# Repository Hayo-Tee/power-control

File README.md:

# Power Control PC by ESP32

[🇷🇺 RU](README_ru.md) | [🇬🇧 EN](README.md)

## Project Description

Recently, I purchased a **Cooler Master Stacker 830** case and built a server PC based on the **ASUS Z10PE-D8** motherboard. Since I access the server via **Tailscale**, I faced a challenge — how to power on the PC remotely if it is completely turned off at home. There are many solutions available online, but I decided to create my own using **ESPHome** and **ESP32-C3**.

---

## Key Features

* **Power on the PC**
* **Power off the PC**
* **Force shutdown** (emulation of holding the power button)
* **Restart the PC**
* **Get PC status** (on / off)

---

## Additional Functionality for Unraid

Since my server runs **Unraid OS**, I added an extra button to control a virtual machine. You can easily repurpose this feature for any other task by modifying the script.

* **Single press** — starts the virtual machine
* **Double press** — stops the virtual machine
* **Long press** — force stops the virtual machine

---

## License

This project is distributed under the **MIT** license.

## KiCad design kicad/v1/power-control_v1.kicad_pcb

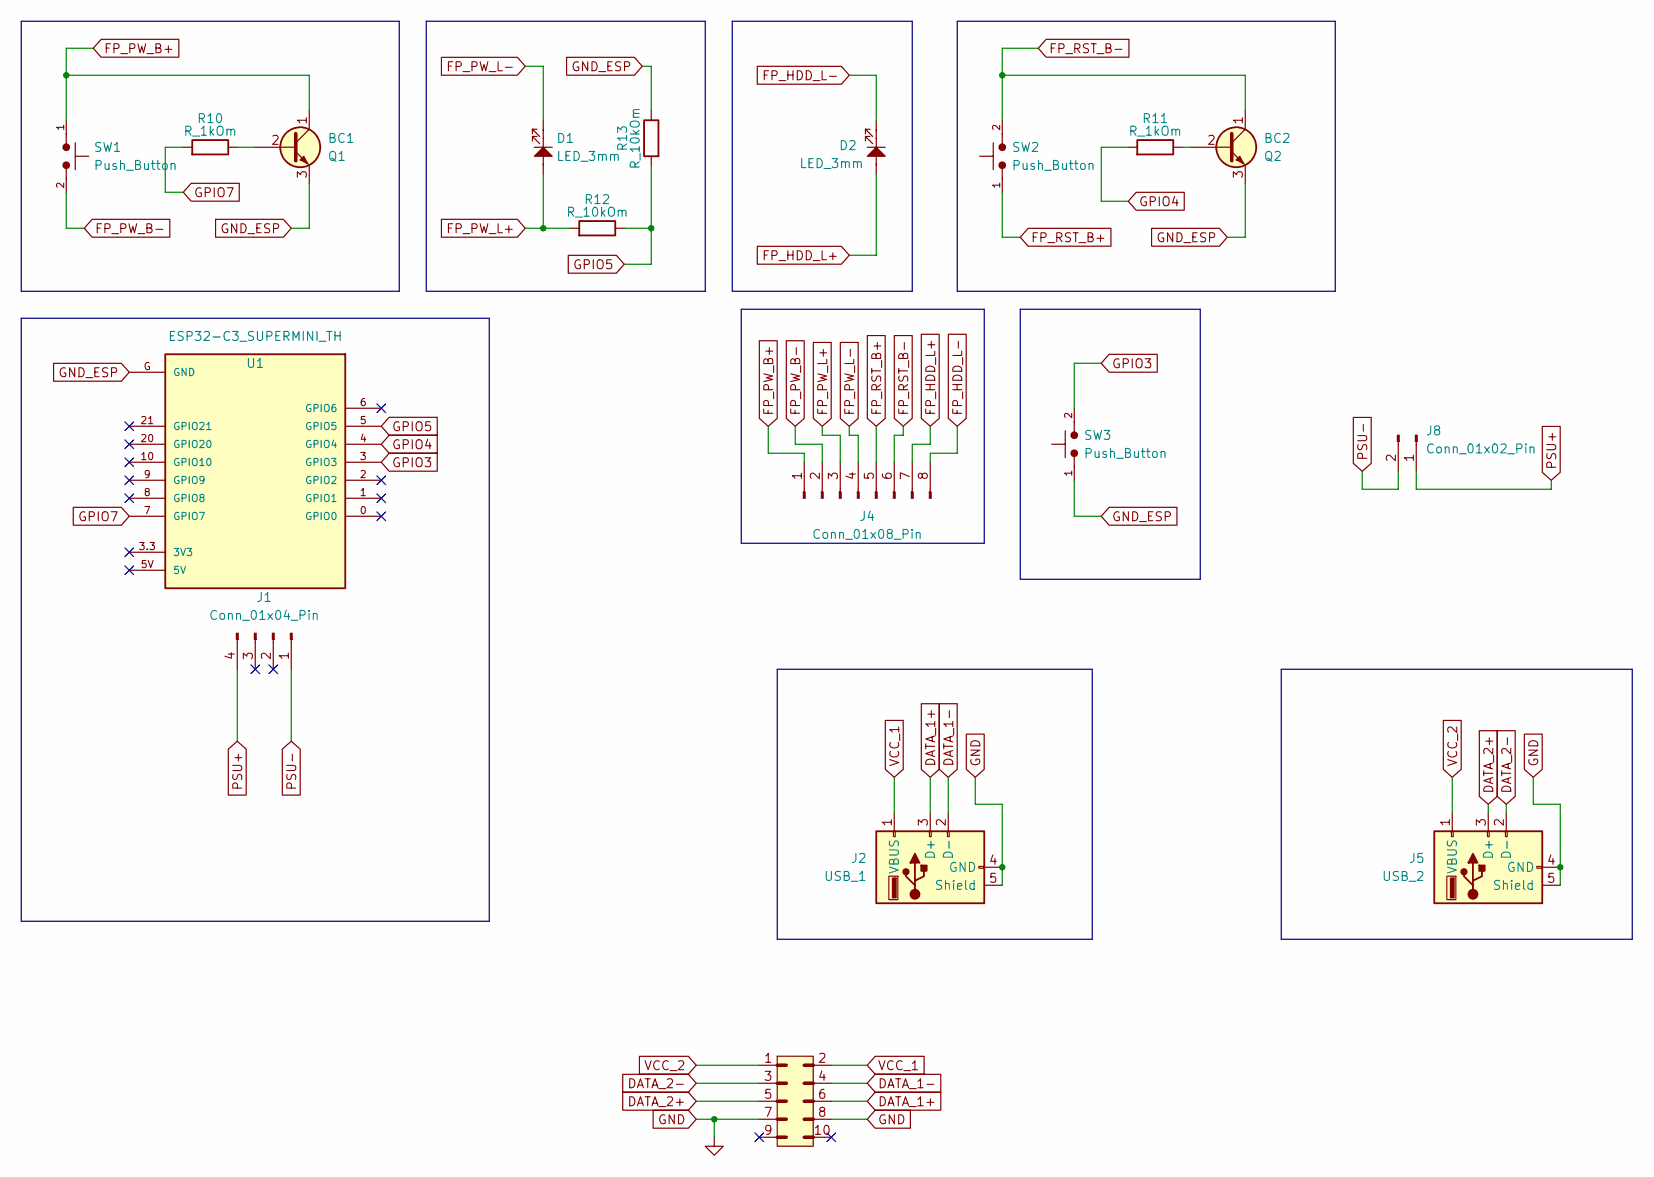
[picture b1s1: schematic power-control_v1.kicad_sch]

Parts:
BC1: Q1; TO-92_Inline_Wide_CBE
BC2: Q2; TO-92_Inline_Wide_CBE
D1, D2: LED_3mm; LED_D3.0mm
J1: Conn_01x04_Pin; PinHeader_1x04_P2.54mm_Vertical
J2: USB_1; ONSHORE_USB-A1VSB6
J4: Conn_01x08_Pin; Connector_MB_FP
J5: USB_2; ONSHORE_USB-A1VSB6
J7: PINHD_2x5_Male; PinHeader_2x05_P2.54mm_Horizontal
J8: Conn_01x02_Pin; JST_XH_B2B-XH-AM_1x02_P2.50mm_Vertical
R10, R11: R_1kOm; R_1206_3216Metric
R12, R13: R_10kOm; R_1206_3216Metric
SW1, SW2, SW3: Push_Button; SW_PUSH_6mm
U1: ESP32-C3_SUPERMINI_TH; MODULE_ESP32-C3_SUPERMINI

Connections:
DATA_1+: J2.3 (D+), J7.6
DATA_1-: J2.2 (D-), J7.4
DATA_2+: J5.3 (D+), J7.5
DATA_2-: J5.2 (D-), J7.3
FP_HDD_L+: D2.2, J4.7
FP_HDD_L-: D2.1, J4.8
FP_PW_B+: BC1.1 (C), J4.1, SW1.1
FP_PW_B-: J4.2, SW1.2
FP_PW_L+: D1.2, J4.3, R12.1
FP_PW_L-: D1.1, J4.4
FP_RST_B+: J4.5, SW2.1
FP_RST_B-: BC2.1 (C), J4.6, SW2.2
GND: J2.4 (GND), J2.5 (Shield), J2.S1, J2.S2, J5.4 (GND), J5.5 (Shield), J5.S1, J5.S2, J7.7, J7.8
GND_ESP: BC1.3 (E), BC2.3 (E), R13.2, SW3.1, U1.G (GND)
GPIO3: SW3.2, U1.3 (GPIO3)
GPIO4: R11.1, U1.4 (GPIO4)
GPIO5: R12.2, R13.1, U1.5 (GPIO5)
GPIO7: R10.1, U1.7 (GPIO7)
unnamed: BC1.2 (B), R10.2
unnamed: BC2.2 (B), R11.2
PSU+: J1.4, J8.1
PSU-: J1.1, J8.2
VCC_1: J2.1 (VBUS), J7.2
VCC_2: J5.1 (VBUS), J7.1

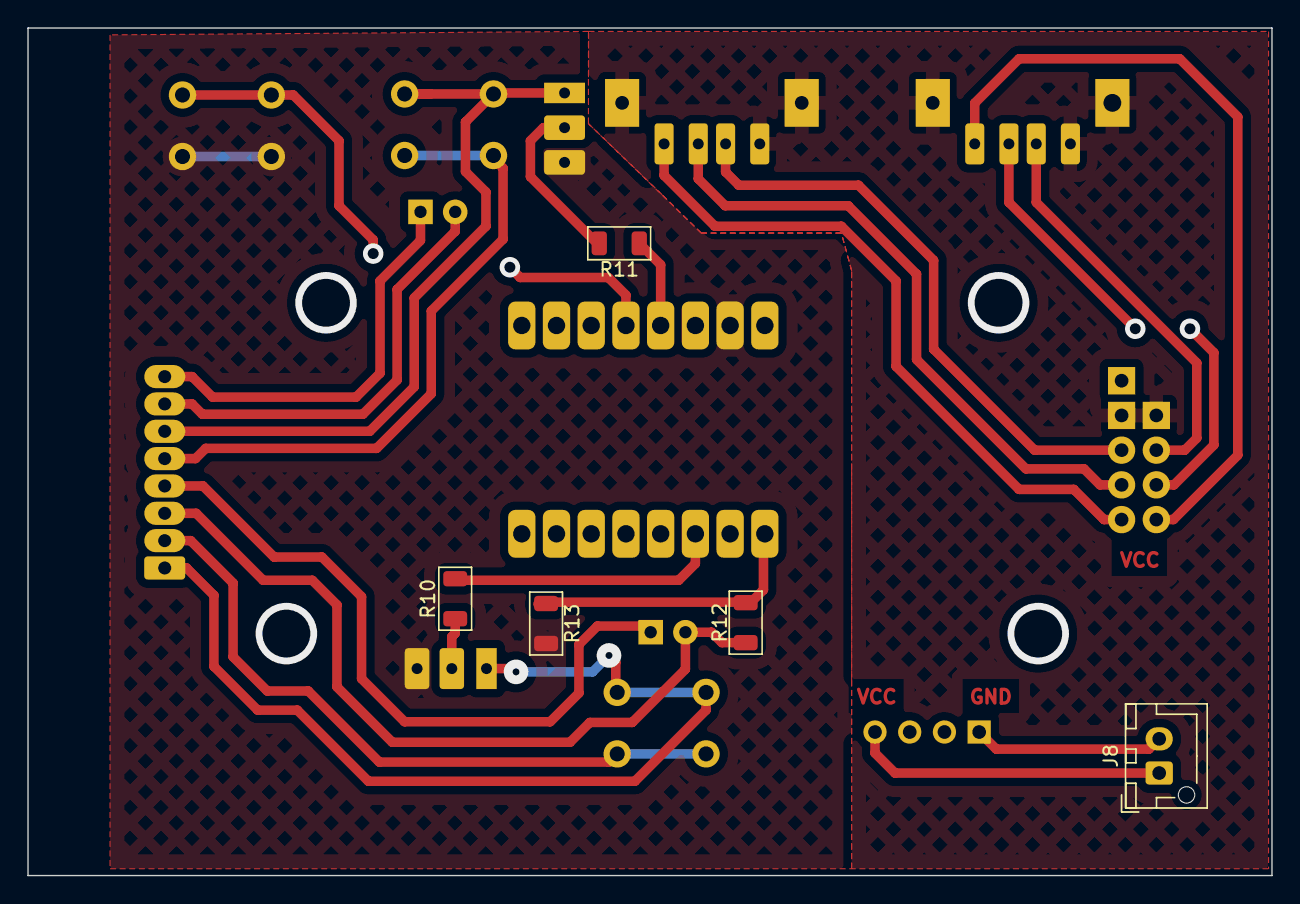
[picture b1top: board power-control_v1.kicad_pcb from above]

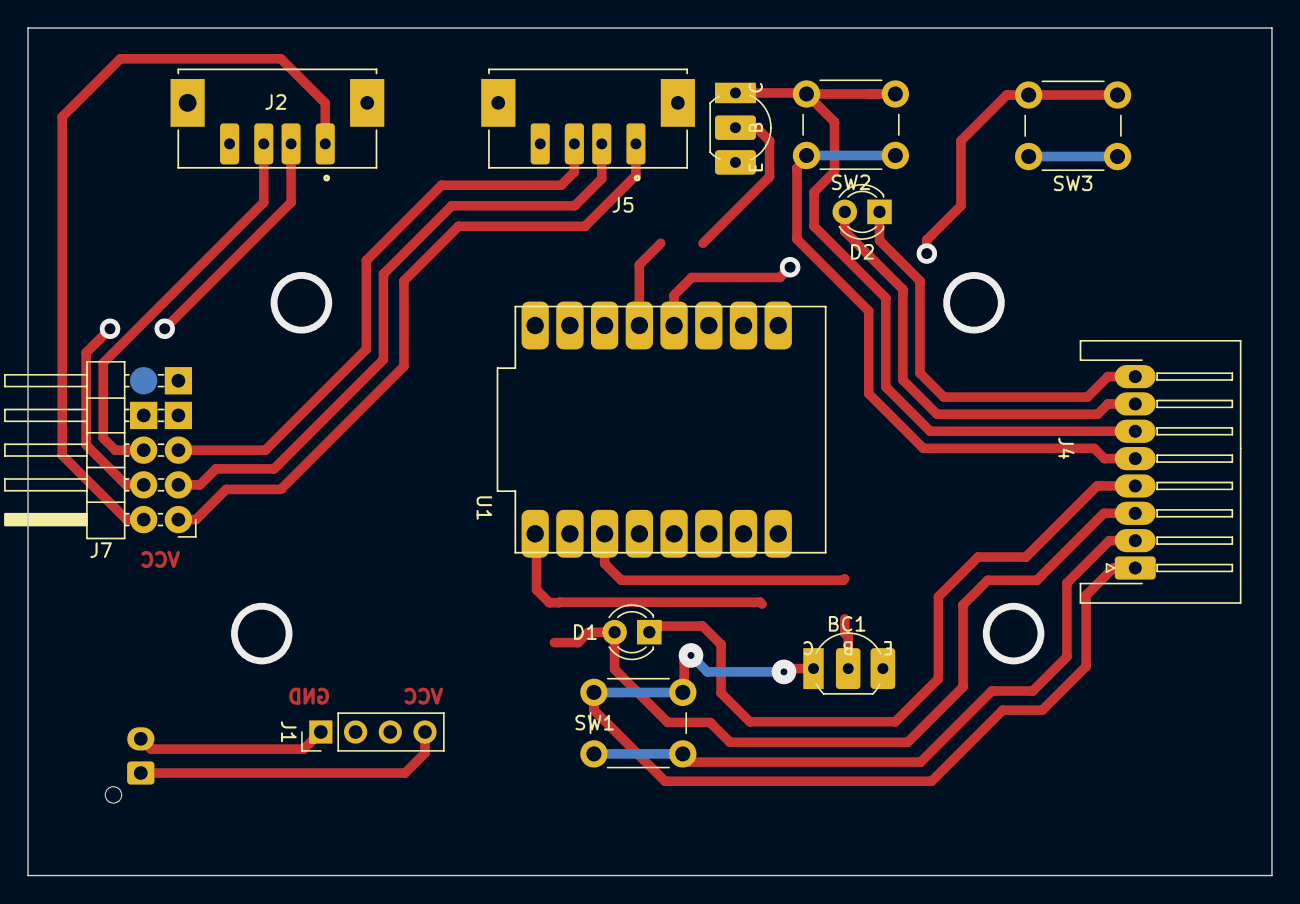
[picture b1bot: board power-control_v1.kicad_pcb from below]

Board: 2 copper layers, 91.0 x 62.0 mm, 18 parts (13 on the bottom side), 24 nets.

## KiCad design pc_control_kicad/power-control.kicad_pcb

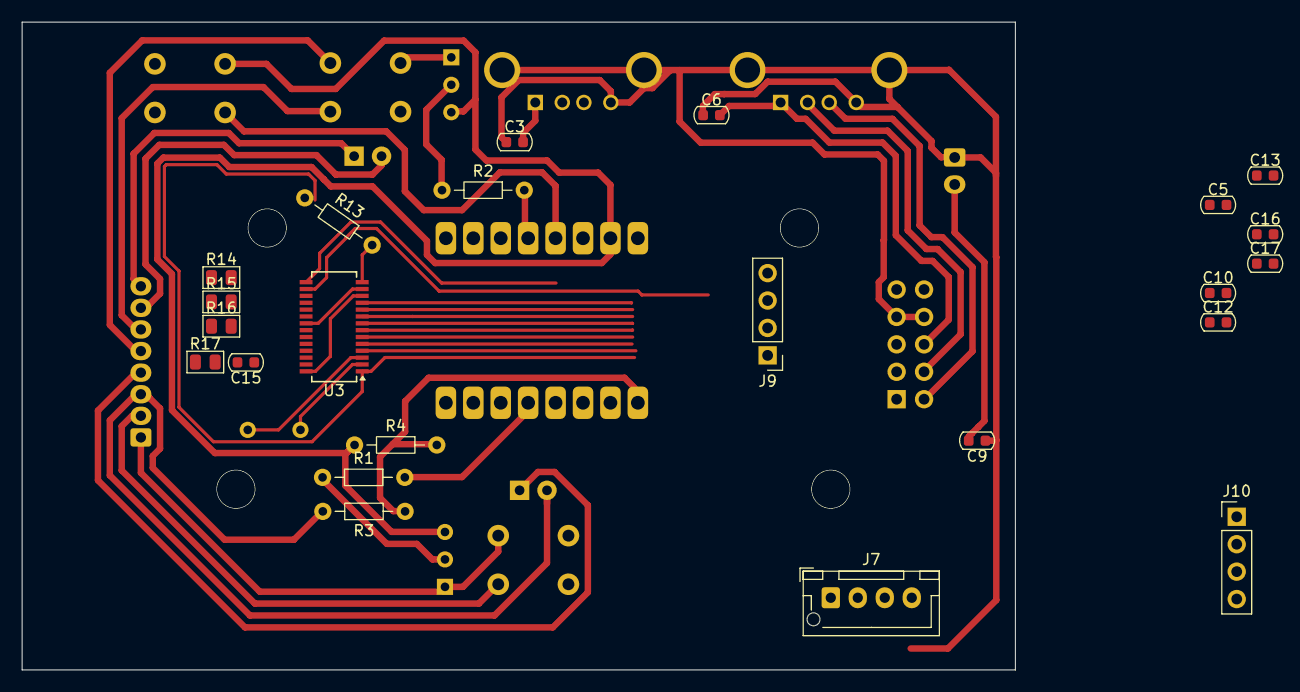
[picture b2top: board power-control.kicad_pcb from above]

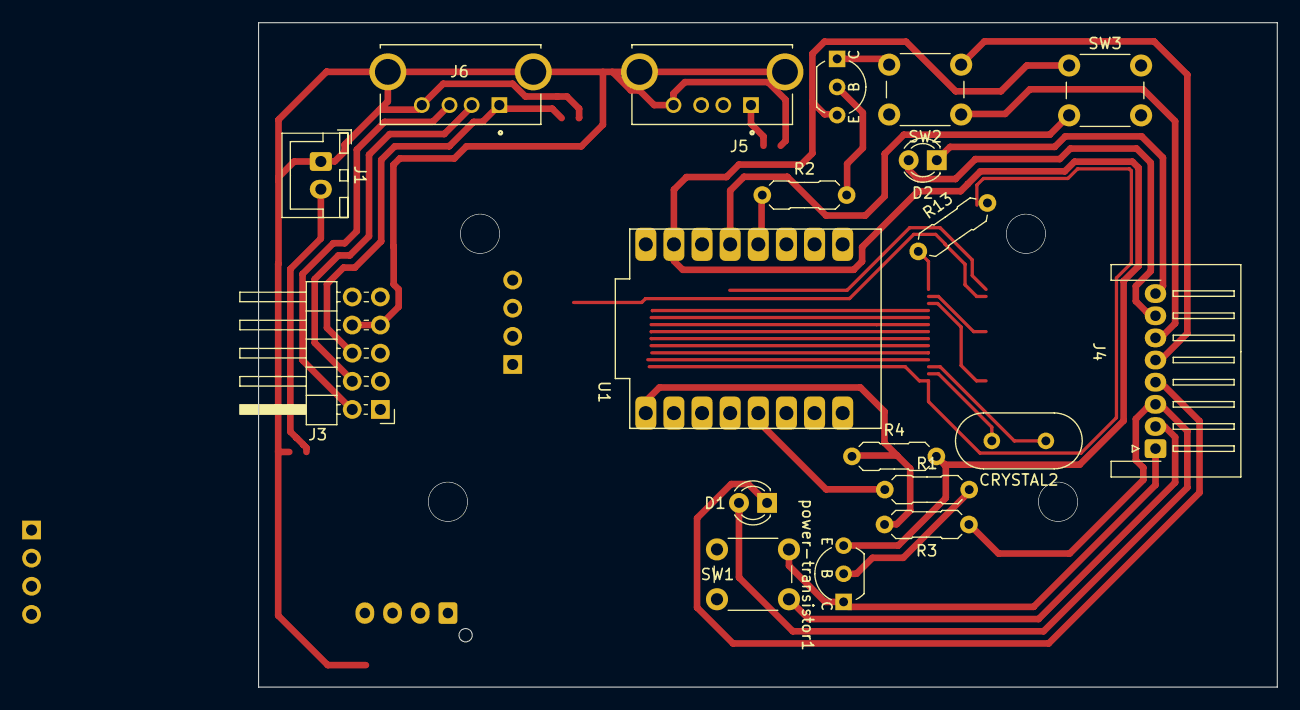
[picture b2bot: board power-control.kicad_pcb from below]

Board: 2 copper layers, 92.0 x 60.0 mm, 37 parts (19 on the bottom side), 39 nets.

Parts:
C3, C5, C6, C10, C12: 100uF_0603; C_0603_1608Metric
C9, C13, C15, C16, C17: 10uF_0603; C_0603_1608Metric
CRYSTAL2: 12 000; Crystal_HC49-4H_Vertical
D1, D2: LED_3mm; LED_D3.0mm
J1: PSU_POWER; JST_XH_B2B-XH-A_1x02_P2.50mm_Vertical
J3: PINHD_2x5_Male; PinHeader_2x05_P2.54mm_Horizontal
J4: Conn_01x08_Pin; Connector_MB_FP
J5, J6: USB_A; ONSHORE_USB-A1VSB6
J7: USB_3_SOCKET; JST_XH_B4B-XH-AM_1x04_P2.50mm_Vertical
J9: Conn_01x04_Pin; PinHeader_1x04_P2.54mm_Vertical
J10: USB_4_SOCKET; PinHeader_1x04_P2.54mm_Vertical
R1, R2: 1kOm; R_Axial_DIN0207_L6.3mm_D2.5mm_P7.62mm_Horizontal
R3, R4: 10kOm; R_Axial_DIN0207_L6.3mm_D2.5mm_P7.62mm_Horizontal
R13: 2.7kOm; R_Axial_DIN0207_L6.3mm_D2.5mm_P7.62mm_Horizontal
R14, R15, R17: R_100kOm; R_0805_2012Metric
R16: R_47kOm; R_0805_2012Metric
SW1, SW2, SW3: Push_Button; SW_PUSH_6mm
U1: ESP32-C3_SUPERMINI_TH; MODULE_ESP32-C3_SUPERMINI
U3: FE1.1s; SSOP-28_3.9x9.9mm_P0.635mm
power-transistor1: BC548; TO-92_Inline_Wide_CBE
reset-transistor1: BC548; TO-92_Inline_Wide_CBE

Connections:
/DATA_1+: J3.2, J6.3 (D+)
/DATA_1-: J3.4, J6.2 (D-)
/DATA_2+: J5.3 (D+), U3.11 (DP1)
/DATA_2-: J5.2 (D-), U3.10 (DM1)
/DATA_3_SOCKET+: J7.3, U3.7 (DP3)
/DATA_3_SOCKET-: J7.2, U3.6 (DM3)
/DATA_4_SOCKET+: J10.3, U3.5 (DP4)
/DATA_4_SOCKET-: J10.2, U3.4 (DM4)
/DATA_U+: J3.1, U3.16 (DPU)
/DATA_U-: J3.3, U3.15 (DMU)
/ESP_USB_DATA+: J9.2, U3.9 (DP2)
/ESP_USB_DATA-: J9.3, U3.8 (DM2)
/FP_HDD_L+: D2.2, J4.7
/FP_HDD_L-: D2.1, J4.8
/FP_PW_B+: J4.1, SW1.1, power-transistor1.1 (C)
/FP_PW_B-: J4.2, SW1.2
/FP_PW_L+: D1.2, J4.3, R3.1 (+)
/FP_PW_L-: D1.1, J4.4
/FP_RST_B+: J4.5, SW2.2, reset-transistor1.1 (C)
/FP_RST_B-: J4.6, SW2.1
/GND_ESP: R4.2 (-), SW3.1, U1.G (GND), power-transistor1.3 (E), reset-transistor1.3 (E)
/GPIO3: R2.1 (+), U1.3 (GPIO3)
/GPIO4: SW3.2, U1.4 (GPIO4)
/GPIO5: R3.2 (-), R4.1 (+), U1.5 (GPIO5)
/GPIO9: R1.1 (+), U1.9 (GPIO9)
/VCC_1: C6.2, J3.6, J6.1 (VBUS)
/VCC_2: C3.2, C5.2, C9.2, C10.1, C12.2, C16.2, C17.1, J1.2, J3.5, J5.1 (VBUS), J7.1, J9.4, J10.1, R16.1, R17.2, U3.20 (VDD5)
/VD_3.3: R14.1, R15.1, U3.26 (OVCJ)
GND: C3.1, C5.1, C6.1, C9.1, C10.2, C12.1, C13.2, C15.2, C16.1, C17.2, J1.1, J3.7, J3.8, J5.4 (GND), J5.S1, J5.S2, J6.4 (GND), J6.S1, J6.S2, J7.4, J9.1, J10.4, R13.2, R17.1, U3.1 (VSS)
unnamed: R1.2 (-), power-transistor1.2 (B)
unnamed: R2.2 (-), reset-transistor1.2 (B)
unnamed: R15.2, U3.19 (BUSJ)
unnamed: R13.1, U3.14 (REXT)
unnamed: R16.2, U3.18 (VBUSM)
unnamed: C15.1, U3.12 (VD18_O), U3.28 (VD18)
unnamed: C13.1, U3.13 (VD33), U3.21 (VD33_O)
unnamed: CRYSTAL2.1, U3.3 (XIN)
unnamed: CRYSTAL2.2, U3.2 (XOUT)
unnamed: R14.2, U3.17 (~XRSTJ)

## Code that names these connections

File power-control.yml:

substitutions:
  power_pin: GPIO7
  reboot_pin: GPIO4
  status_pin: GPIO5
  button_pin: GPIO3
  api_key: !secret power_control_api
  wifi_ssid: !secret wifi_ssid
  wifi_password: !secret wifi_password
  ap_password: !secret ap_password
  server_url: "http://server:8080"

esphome:
  name: pc-power-control
  friendly_name: "PC Power"
  platformio_options:
    build_flags:
      - '-DCONFIG_ESP_CONSOLE_USB_CDC=n'

esp32:
  board: esp32-c3-devkitm-1
  framework:
    type: arduino

uart:
  id: uart_bus
  tx_pin: GPIO21
  rx_pin: GPIO20
  baud_rate: 115200
  data_bits: 8
  parity: NONE
  stop_bits: 1

logger:
  level: DEBUG
  baud_rate: 115200
  logs:
    component.gpio: DEBUG
    multi_click: DEBUG

web_server:
  port: 80

ota:
  - platform: esphome
    password: 1507
  - platform: web_server

wifi:
  ssid: ${wifi_ssid}
  password: ${wifi_password}
  ap:
    ssid: "PC-Control-Fallback"
    password: ${ap_password}

http_request:
  useragent: esphome/pc-power-control
  timeout: 5s
  verify_ssl: false

output:
  - platform: gpio
    pin: ${power_pin}
    id: power_button_output
  - platform: gpio
    pin: ${reboot_pin}
    id: reboot_button_output

binary_sensor:
  - platform: gpio
    pin:
      number: ${status_pin}
      mode: input
    name: "PC Status"
    device_class: power
    id: pc_status

  - platform: gpio
    pin:
      number: ${button_pin}
      mode: INPUT_PULLUP
      inverted: true
    name: "Physical Button"
    id: physical_button
    internal: true
    filters:
      - delayed_on: 100ms  # Уменьшил задержку для более быстрого реагирования
      - delayed_off: 100ms
    on_multi_click:
      - timing:
          - ON for at most 0.3s  # Быстрое нажатие
          - OFF for at least 0.1s  # Минимальная пауза
          - ON for at most 0.3s  # Второе быстрое нажатие
          - OFF for at least 0.1s
        then:
          - logger.log: "Double press detected - stopping VM"
          - http_request.get:
              url: "${server_url}/stop_win.sh"
      - timing:
          - ON for at most 0.5s  # Одиночное нажатие
          - OFF for at least 0.3s
        then:
          - logger.log: "Single press detected - starting VM"
          - http_request.get:
              url: "${server_url}/start_win.sh"
      - timing:
          - ON for at least 4s  # Длинное нажатие (уменьшил время)
          - OFF for at least 0.3s
        then:
          - logger.log: "Long press detected - force stopping VM"
          - http_request.get:
              url: "${server_url}/destroy_win.sh"

sensor:
  - platform: uptime
    name: "Uptime"
  - platform: wifi_signal
    name: "WiFi Signal"
    update_interval: 60s

text_sensor:
  - platform: wifi_info
    ip_address:
      name: "IP Address"

button:
  - platform: template
    name: "Turn On PC"
    icon: "mdi:power"
    entity_category: "config"
    on_press:
      if:
        condition:
          binary_sensor.is_off: pc_status
        then:
          - output.turn_on: power_button_output
          - delay: 500ms
          - output.turn_off: power_button_output
          - http_request.get:
              url: "${server_url}/start_win.sh"

  - platform: template
    name: "Soft Shutdown PC"
    icon: "mdi:power-standby"
    entity_category: "config"
    on_press:
      if:
        condition:
          binary_sensor.is_on: pc_status
        then:
          - http_request.get:
              url: "${server_url}/stop_win.sh"
          - delay: 5s
          - output.turn_on: power_button_output
          - delay: 1s
          - output.turn_off: power_button_output

  - platform: template
    name: "Force Shutdown PC"
    icon: "mdi:power-off"
    entity_category: "config"
    on_press:
      if:
        condition:
          binary_sensor.is_on: pc_status
        then:
          - http_request.get:
              url: "${server_url}/destroy_win.sh"
          - delay: 5s
          - output.turn_on: power_button_output
          - delay: 5s
          - output.turn_off: power_button_output

  - platform: template
    name: "Reboot PC"
    icon: "mdi:restart-alert"
    entity_category: "config"
    on_press:
      - output.turn_on: reboot_button_output
      - delay: 500ms
      - output.turn_off: reboot_button_output

  - platform: template
    name: "Start VM"
    icon: "mdi:server"
    entity_category: "config"
    on_press:
      - http_request.get:
          url: "${server_url}/start_win.sh"

  - platform: template
    name: "Stop VM"
    icon: "mdi:server-off"
    entity_category: "config"
    on_press:
      - http_request.get:
          url: "${server_url}/stop_win.sh"

  - platform: template
    name: "Force Stop VM"
    icon: "mdi:server-remove"
    entity_category: "config"
    on_press:
      - http_request.get:
          url: "${server_url}/destroy_win.sh"

interval:
  - interval: 6h
    then:
      - logger.log: "Scheduled ESP32 restart (every 6 hours)"
      - lambda: |-
          ESP.restart();

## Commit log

2025-03-01 Create wol.yaml
    working wol state
2025-03-19 Update pc_control.yaml
    Power button and reset working
2025-03-19 Update pc_control.yaml
    vm control settings
2025-03-19 Create vm_control
2025-03-19 Rename vm_control to vm_control.sh
2025-05-22 kicad
2025-08-11 full update
2025-08-11 update 1
2025-08-11 update 3
2025-08-11 update 4
2025-08-12 update 5
2025-08-12 update 6
2025-08-18 Photo of PCB
